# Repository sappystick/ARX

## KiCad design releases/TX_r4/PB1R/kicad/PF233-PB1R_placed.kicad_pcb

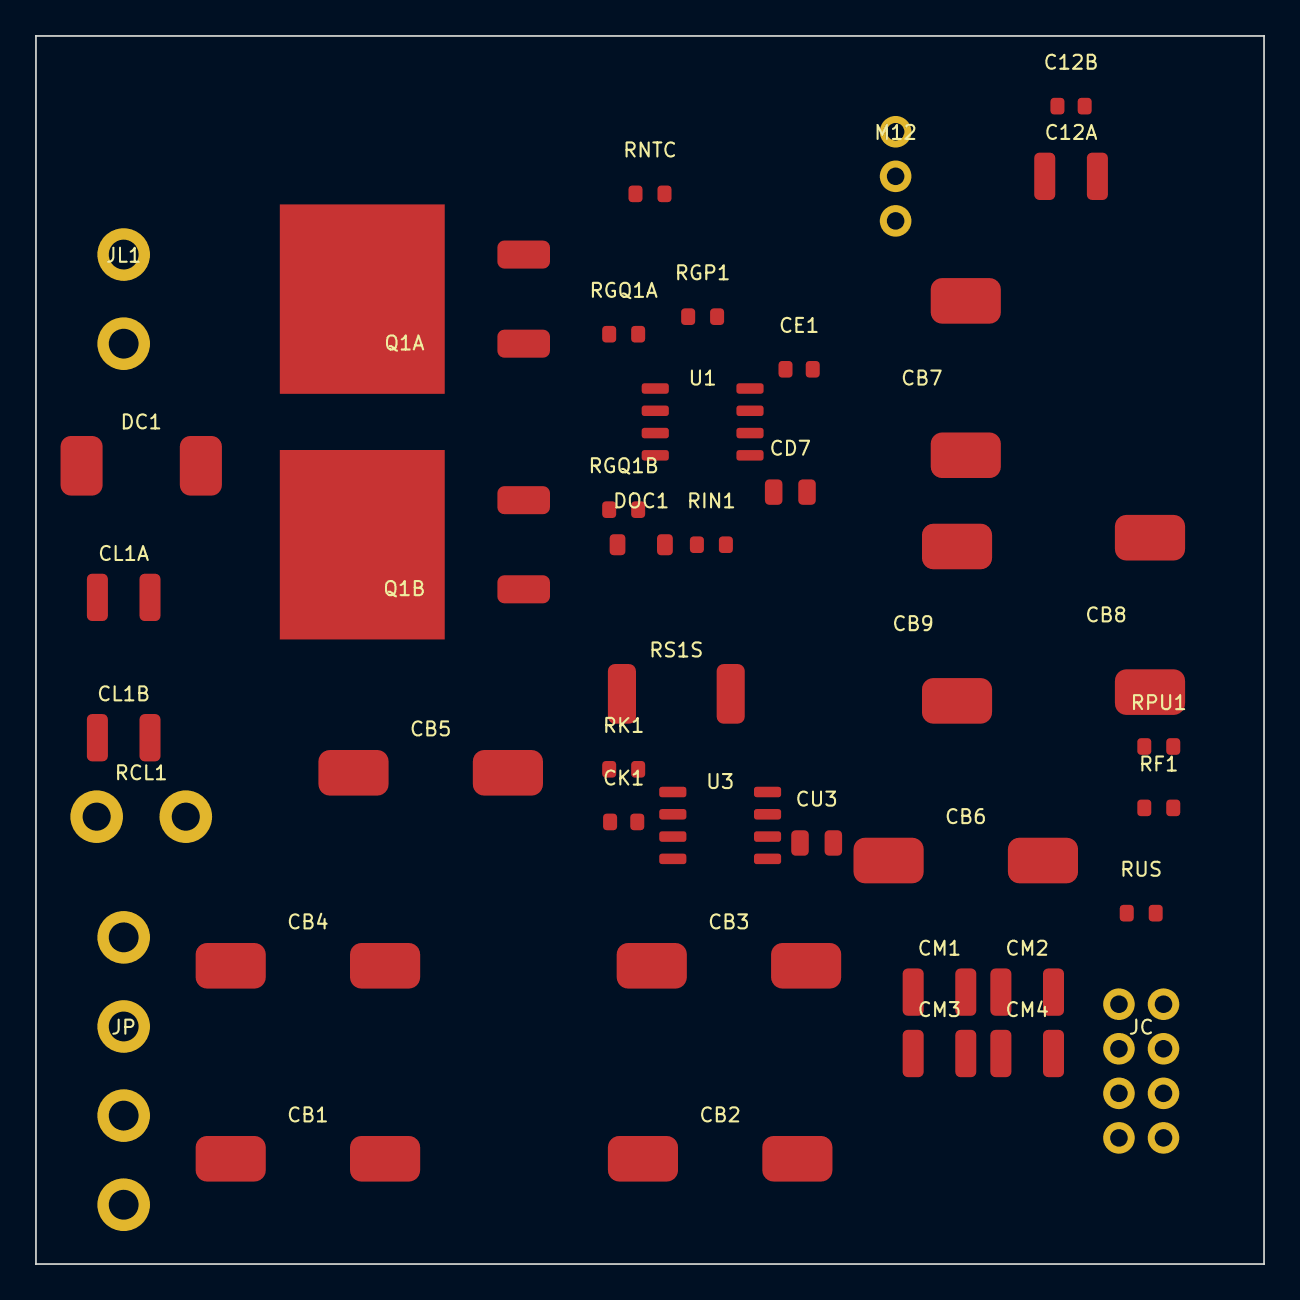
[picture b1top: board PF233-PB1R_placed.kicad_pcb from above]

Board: 4 copper layers, 70.0 x 70.0 mm, 42 parts (0 on the bottom side), 17 nets, no tracks yet.

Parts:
C12A: 22u 25V; C_1210_3225Metric
C12B: 100n; C_0603_1608Metric
CB1, CB2, CB3, CB4, CB5, CB6, CB7, CB8, CB9: 100u 50V hybrid; CP_Elec_10x10
CD7: 1u 25V; C_0805_2012Metric
CE1: 100n; C_0603_1608Metric
CK1: 100p; C_0603_1608Metric
CL1A, CL1B: 100n 630V; C_1210_3225Metric
CM1, CM2, CM3, CM4: 10u 50V; C_1210_3225Metric
CU3: 1u 25V; C_0805_2012Metric
DC1: ES3J 600V 3A; D_SMC
DOC1: BAS16; D_SOD-123
JC: Umbilical from the head: SHLD GND TX1_IN REF_I1 F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; Pin_header_2x4_P2.54mm
JL1: Coil outer band: DRAIN, VBUS; Terminal_block_1x2_P5.08mm
JP: Power in: VBUS VBUS GND GND; Terminal_block_1x4_P5.08mm
M12: 12 V 1.0 A switching module; Converter_DCDC_Murata_OKI-78SR_Horizontal
Q1A, Q1B: 650V SJ 95mR; TO-263-3_TabPin2
RCL1: external 5k 10W (lid bank); SolderPad_2x_P5.08mm
RF1: 1k; R_0603_1608Metric
RGP1: 10k; R_0603_1608Metric
RGQ1A, RGQ1B: 10; R_0603_1608Metric
RIN1: 100; R_0603_1608Metric
RK1: 100; R_0603_1608Metric
RNTC: 10k NTC; R_0603_1608Metric
RPU1: 10k; R_0603_1608Metric
RS1S: 10m 1W; R_2512_6332Metric
RUS: 1M; R_0603_1608Metric
U1: TC4420; SOIC-8_3.9x4.9mm_P1.27mm
U3: LM393; SOIC-8_3.9x4.9mm_P1.27mm

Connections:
AUX12: C12A.1, C12B.1, CD7.1, CE1.1, CU3.1, M12.3, RPU1.2, U1.1, U1.8, U3.8
CLAMP1: CL1A.1, CL1B.1, DC1.1, RCL1.1
DRAIN1: DC1.2, JL1.1, Q1A.2, Q1B.2
DRVIN1: DOC1.2, RIN1.2, U1.2
FAULT1_N: JC.5, RF1.2
G1: RGP1.1, RGQ1A.1, RGQ1B.1, U1.6, U1.7
GATE_Q1A: Q1A.1, RGQ1A.2
GATE_Q1B: Q1B.1, RGQ1B.2
GND: C12A.2, C12B.2, CB1.2, CB2.2, CB3.2, CB4.2, CB5.2, CB6.2, CB7.2, CB8.2, CB9.2, CD7.2, CE1.2, CK1.2, CM1.2, CM2.2, CM3.2, CM4.2, CU3.2, JC.2, JC.8, JP.3, JP.4, M12.2, RGP1.2, RNTC.2, RS1S.2, RUS.2, U1.4, U1.5, U3.4, U3.5, U3.6
ISENSE1: CK1.1, JC.6, RK1.2, U3.2
NTC_SENSE: JC.7, RNTC.1
OC1_OUT: DOC1.1, RF1.1, RPU1.1, U3.1
REF_I1: JC.4, U3.3
SRC1: Q1A.3, Q1B.3, RK1.1, RS1S.1
TX1_IN: JC.3, RIN1.1
UMB_SHLD: JC.1, RUS.1
VBUS: CB1.1, CB2.1, CB3.1, CB4.1, CB5.1, CB6.1, CB7.1, CB8.1, CB9.1, CL1A.2, CL1B.2, CM1.1, CM2.1, CM3.1, CM4.1, JL1.2, JP.1, JP.2, M12.1, RCL1.2

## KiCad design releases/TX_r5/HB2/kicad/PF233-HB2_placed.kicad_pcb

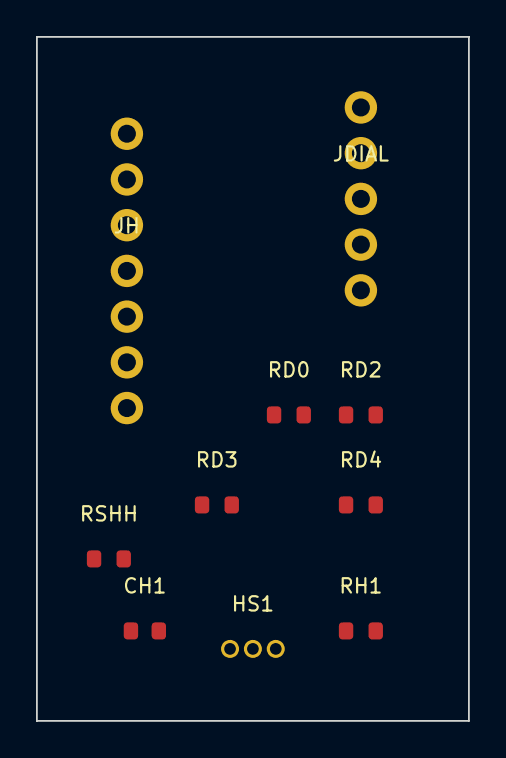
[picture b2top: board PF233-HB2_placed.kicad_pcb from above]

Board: 4 copper layers, 24.0 x 38.0 mm, 10 parts (0 on the bottom side), 9 nets, no tracks yet.

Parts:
CH1: 100n; C_0603_1608Metric
HS1: Hall switch OD; TO-92_Inline
JDIAL: Dial: COM P1 P2 P3 P4 (4-pos rotary, top housing); Pin_header_1x5_P2.54mm
JH: Signal cord to the head: +3V3 GND TRIG DIAL - - S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; Pin_header_1x7_P2.54mm
RD0, RD3: 10k; R_0603_1608Metric
RD2: 3k3; R_0603_1608Metric
RD4: 33k; R_0603_1608Metric
RH1: 1k; R_0603_1608Metric
RSHH: 0R; R_0603_1608Metric

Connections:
DIAL: JDIAL.1, JH.4, RD0.2
DP2: JDIAL.3, RD2.1
DP3: JDIAL.4, RD3.1
DP4: JDIAL.5, RD4.1
GND: CH1.2, HS1.2, JDIAL.2, JH.2, RD2.2, RD3.2, RD4.2, RSHH.2
HALL_OUT: HS1.3, RH1.1
P3V3: CH1.1, HS1.1, JH.1, RD0.1
SHIELD: JH.7, RSHH.1
TRIG: JH.3, RH1.2
